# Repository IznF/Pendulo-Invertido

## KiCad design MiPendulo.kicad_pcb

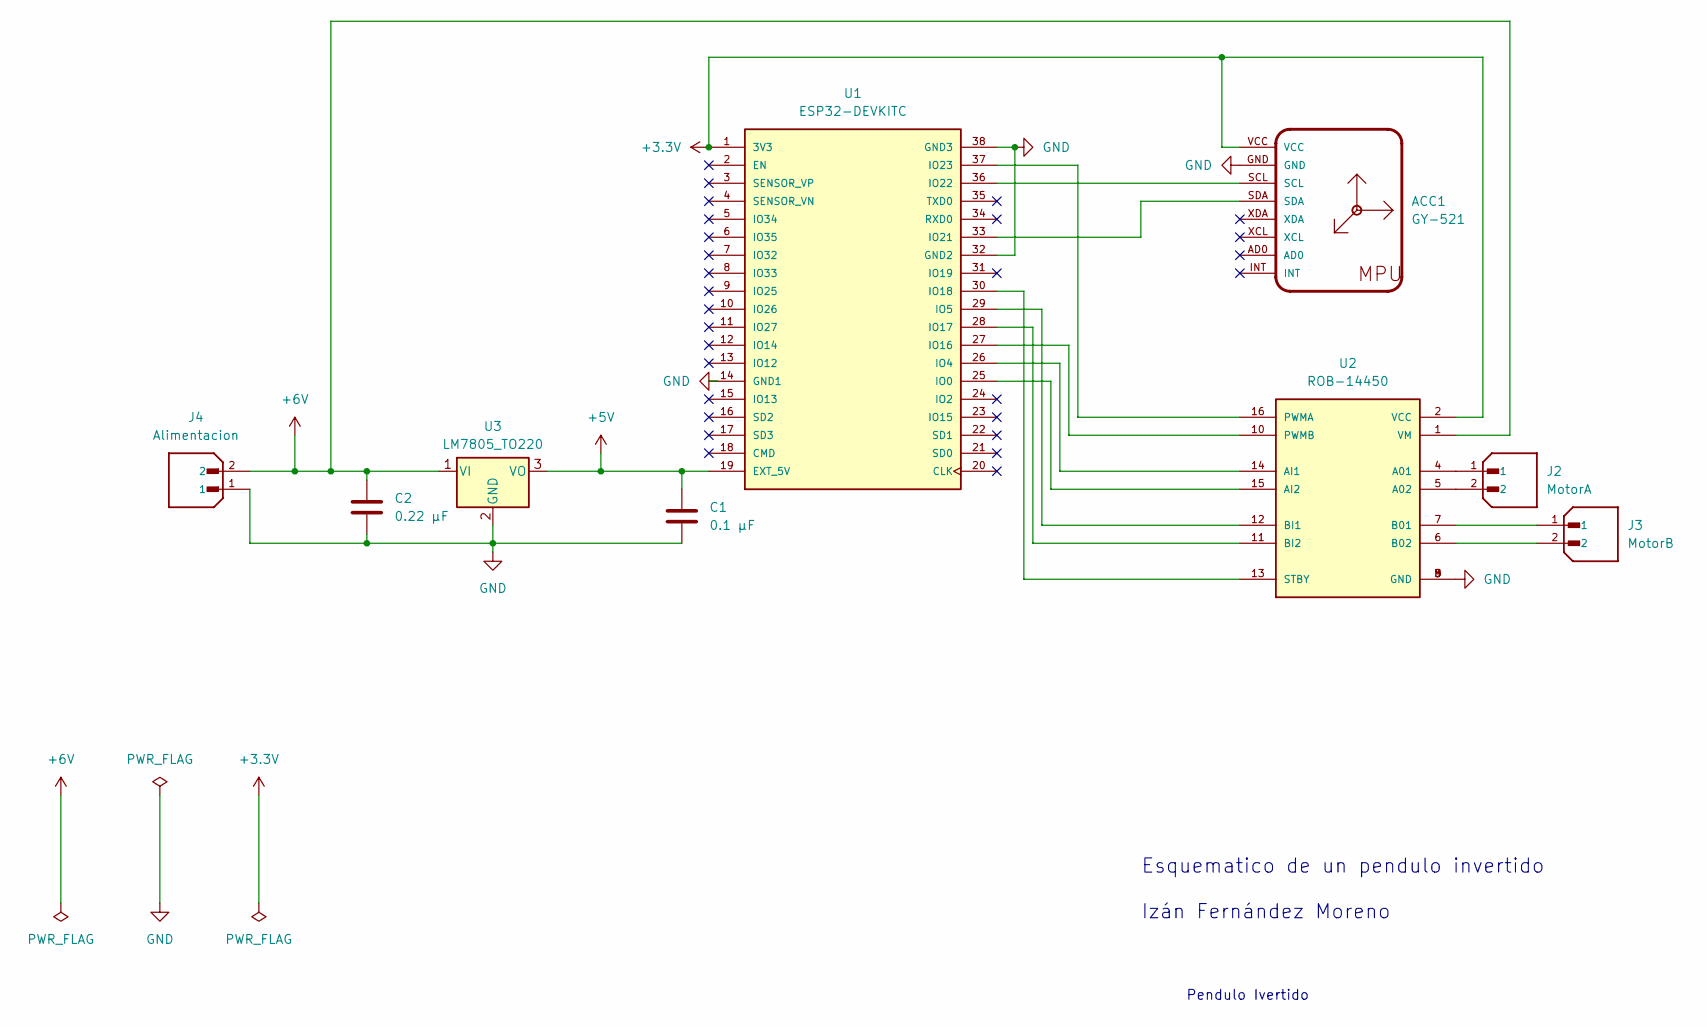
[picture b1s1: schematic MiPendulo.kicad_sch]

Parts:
ACC1: GY-521
C1: 0.1 µF; CP_Radial_D4.0mm_P2.00mm
C2: 0.22 µF; CP_Radial_D5.0mm_P2.50mm
J2: MotorA; JST_B2B-XH-A__LF__SN_; PARTREV N/A
J3: MotorB; JST_B2B-XH-A__LF__SN_; PARTREV N/A
J4: Alimentacion; JST_B2B-XH-A__LF__SN_; PARTREV N/A
U1: ESP32-DEVKITC; MODULE_ESP32-DEVKITC; PARTREV N/A
U2: ROB-14450; MODULE_ROB-14450; PARTREV 11-13-17
U3: LM7805_TO220; TO-220-3_Vertical

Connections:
+3.3V: ACC1.VCC, U1.1 (3V3), U2.2 (VCC)
+5V: C1.1, U1.19 (EXT_5V), U3.3 (VO)
+6V: C2.1, J4.2, U2.1 (VM), U3.1 (VI)
GND: ACC1.GND, C1.2, C2.2, J4.1, U1.14 (GND1), U1.32 (GND2), U1.38 (GND3), U2.3 (GND), U2.8 (GND), U2.9 (GND), U3.2 (GND)
unnamed: U1.25 (IO0), U2.15 (AI2)
unnamed: U1.26 (IO4), U2.14 (AI1)
unnamed: U1.29 (IO5), U2.12 (BI1)
unnamed: U1.27 (IO16), U2.10 (PWMB)
unnamed: U1.28 (IO17), U2.11 (BI2)
unnamed: U1.30 (IO18), U2.13 (STBY)
unnamed: ACC1.SDA, U1.33 (IO21)
unnamed: ACC1.SCL, U1.36 (IO22)
unnamed: U1.37 (IO23), U2.16 (PWMA)
unnamed: J2.1, U2.4 (A01)
unnamed: J2.2, U2.5 (A02)
unnamed: J3.1, U2.7 (B01)
unnamed: J3.2, U2.6 (B02)

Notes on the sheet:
Pendulo Ivertido
Esquematico de un pendulo invertido Izán Fernández Moreno

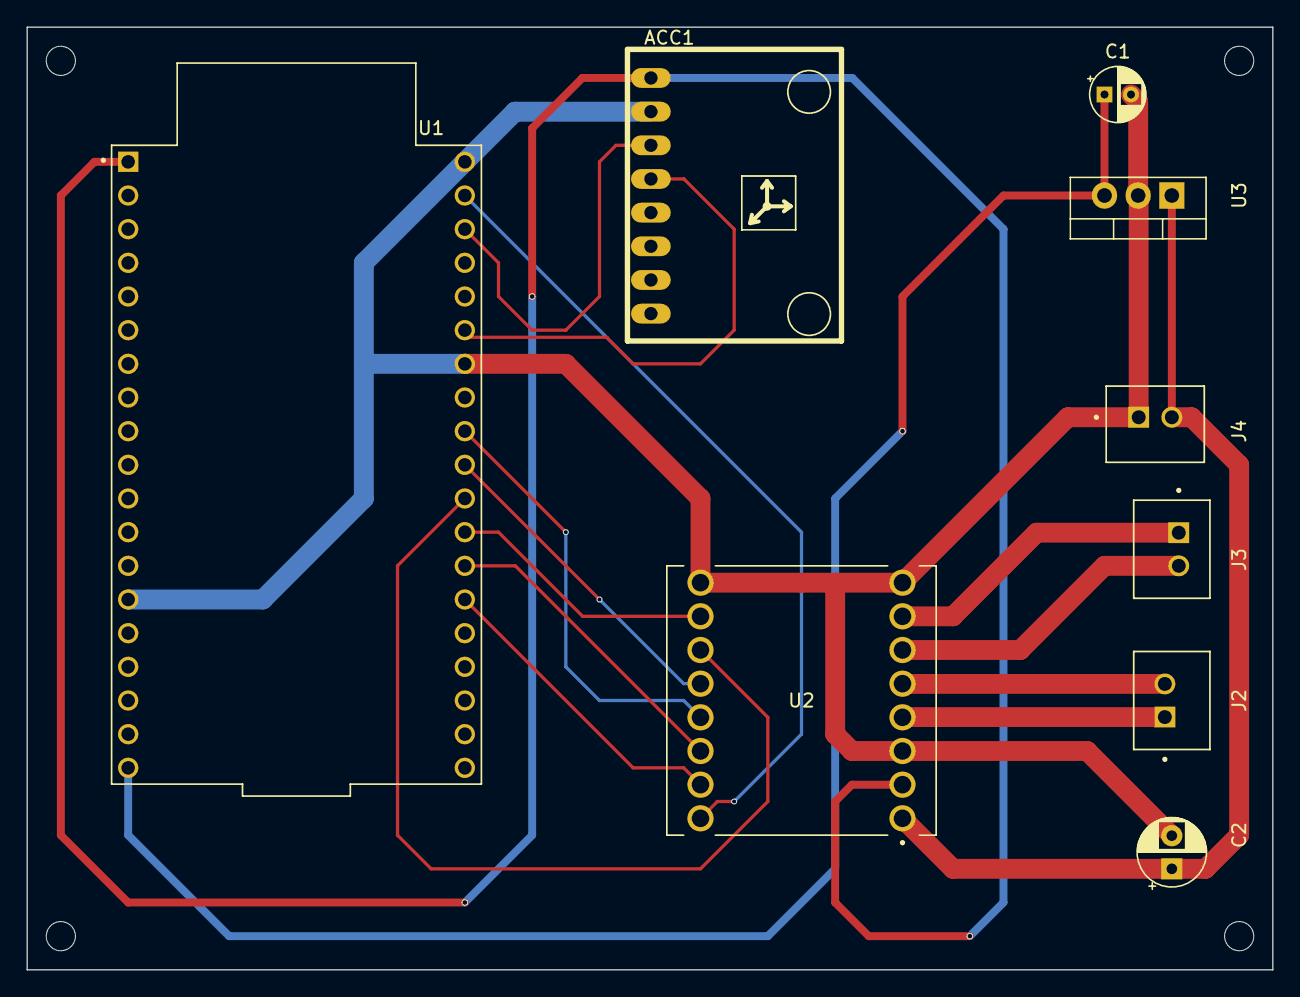
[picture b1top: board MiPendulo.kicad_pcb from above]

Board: 2 copper layers, 94.0 x 71.1 mm, 9 parts (0 on the bottom side), 17 nets.
